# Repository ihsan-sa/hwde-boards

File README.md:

# hwde-boards

KiCad board designs made with [hwde](https://github.com/ihsan-sa/hwde), an AI PCB design skill for
Claude Code that takes a board from a written brief to a JLCPCB order. Each folder is one board's
whole workspace: the brief, research notes, architecture, parts choices, the KiCad project,
routing work, review reports, logs, and the fab package.

Every board has a part number of the form **PCB-NNNN-R**: four digits for the product, then a
revision letter. `register.yaml` lists them.

## The boards

Layers and size come from each board's KiCad file. Stage is the hwde phase recorded in the board's
`state.json`: P3 parts, P4 schematic, P7 routing, P8 verification, P9 DFM and fab outputs, P10 ordering.

| Number | What it is | Layers | Size (mm) | Stage |
|---|---|---|---|---|
| [PCB-0001-A](PCB-0001-A_stm32-blinky) | STM32F103 2-layer blinky dev board | 2 | 50 x 40 | P10 |
| [PCB-0002-A](PCB-0002-A_usb-buck) | STM32F103 4-layer USB device board with 3.3 V buck | 4 | 50 x 40 | P10 |
| [PCB-0003-A](PCB-0003-A_pd-trigger) | USB-C PD trigger, 5 A / 100 W bench board | 2 | 48 x 30 | P10 |
| [PCB-0004-A](PCB-0004-A_lumina-carrier) | LUMINA PoE ESP32 carrier | 4 | 100 x 80 | P10 |
| [PCB-0005-A](PCB-0005-A_lumina-par) | LUMINA RGB+W par light daughter board | 4 | 100 x 80 | P8, no fab package |
| [PCB-0006-A](PCB-0006-A_lumina-strobe) | LUMINA strobe daughter board | - | - | P4, no board yet |
| [PCB-0007-A](PCB-0007-A_rf-de-20m) | 20 MHz Class E GaN RF power stage, 200 W | 4 | 120 x 80 | P9, see its `fab/README.md` |
| [PCB-0008-A](PCB-0008-A_buck-5v3a) | 12 V to 5 V / 3 A synchronous buck, first attempt | - | - | closed at P3, never built |
| [PCB-0008-B](PCB-0008-B_sbuck-5v3a) | 12 V to 5 V / 3 A synchronous buck | 4 | 50 x 40 | P10 |
| [PCB-0009-A](PCB-0009-A_rf-term-150w) | 50 ohm / 150 W RF termination | 2 | 26 x 20 | P9 |
| [PCB-0010-A](PCB-0010-A_bb-buck) | Bare-bones 24 V to 5 V / 2 A buck | 2 | 35 x 25 | P9 |
| [PCB-0011-A](PCB-0011-A_bb-mcu) | Block-basics microcontroller board | 2 | 34.8 x 22.3 | P9 |
| [PCB-0012-A](PCB-0012-A_bb-ldo) | Block-basics 5 V to 3.3 V / 500 mA LDO | 2 | 34.7 x 34.7 | P9 |
| [PCB-0013-A](PCB-0013-A_bb-amp) | Block-basics bridge-sensor amplifier | 2 | 48.0 x 28.3 | P9 |
| [PCB-0014-A](PCB-0014-A_bb-adc) | Block-basics 12-bit single-channel ADC | 2 | 54.8 x 34.9 | P9 |
| [PCB-0015-A](PCB-0015-A_g0-sense) | USB-C STM32G0 temperature/humidity sensor node | 2 | 35.8 x 28.3 | P10 |
| [PCB-0016-A](PCB-0016-A_pd-trigger-lite) | Low-cost USB-C PD trigger (CH224K) | 2 | 25 x 15 | P8 |
| [PCB-0016-B](PCB-0016-B_pd-trigger-lite-dip) | The same, voltage picked with a DIP switch | 2 | 25 x 21 | P9 |
| [PCB-0017-A](PCB-0017-A_stereo-class-d-amp) | TPA3118D2 stereo class-D amplifier, 12 V | 2 | 53.5 x 36.8 | P7 |
| [PCB-0018-A](PCB-0018-A_bldc-motor-driver) | 3-phase BLDC motor driver, 10-28 V, 10 A RMS/phase, STM32G4 FOC | 4 | 78 x 78 | P9 |
| [PCB-0020-A](PCB-0020-A_esp32c3-node) | ESP32-C3 WiFi/BLE sensor node, USB-C, 1S LiPo, BME280 | 2 | 26 x 38 | P8 |
| [PCB-0021-A](PCB-0021-A_lipo-boost) | Single-cell LiPo charger + 5 V / 1 A boost with load sharing | 2 | 53.9 x 38.8 | P9 |

All boards with a fab package are 1.6 mm thick.

## Where things are in a board folder

- `kicad/` the KiCad project (`.kicad_pro`, `.kicad_sch`, `.kicad_pcb`); it was made with KiCad 10, so open it with KiCad 10.
- `fab/` the order package: `<folder>_gerbers.zip`, `BOM.csv` and `CPL.csv` in JLCPCB's format.
- `reports/` review reports, renders, a schematic PDF for every board that has a schematic, and a
  design document PDF for most of them.
- `brief/`, `requirements.md`, `research/`, `architecture/`, `parts/` why the board is the way it is.
- `state.json` the phase, the gates that passed, and every decision hwde recorded.

## Ordering a board from JLCPCB

1. On jlcpcb.com, start a PCB order and upload the board's `fab/<folder>_gerbers.zip`. Set the
   layer count and thickness to match the table above.
2. To have JLCPCB assemble it, turn on PCB Assembly and upload `fab/BOM.csv` as the BOM and
   `fab/CPL.csv` as the pick-and-place file.
3. Check the part matches and the placement preview before you pay. Stock changes, so a part may
   need a substitute from the same footprint.

Read the board's reports first. Unless a board's own documents say it was built and tested, treat
the design as unverified on real hardware.

## What is not included

- **3D models.** Vendor STEP and WRL models are not redistributed, so footprints that pointed at
  them show no 3D body in KiCad's 3D viewer. The copper, silkscreen and fab outputs are unaffected.
- **Datasheets and app notes.** Vendor PDFs and copies of vendor pages are left out. The research
  notes and `parts/` records still cite them by name and part number.
- Order and shipment records, and a few design documents whose text carried private details.
  Their LaTeX sources are still under `reports/`.

Some files keep absolute paths from the machine a board was designed on (for example
`C:/Users/<user>/...`). They are records of a run and are not needed to open the design.

## License

MIT, see [LICENSE](LICENSE).

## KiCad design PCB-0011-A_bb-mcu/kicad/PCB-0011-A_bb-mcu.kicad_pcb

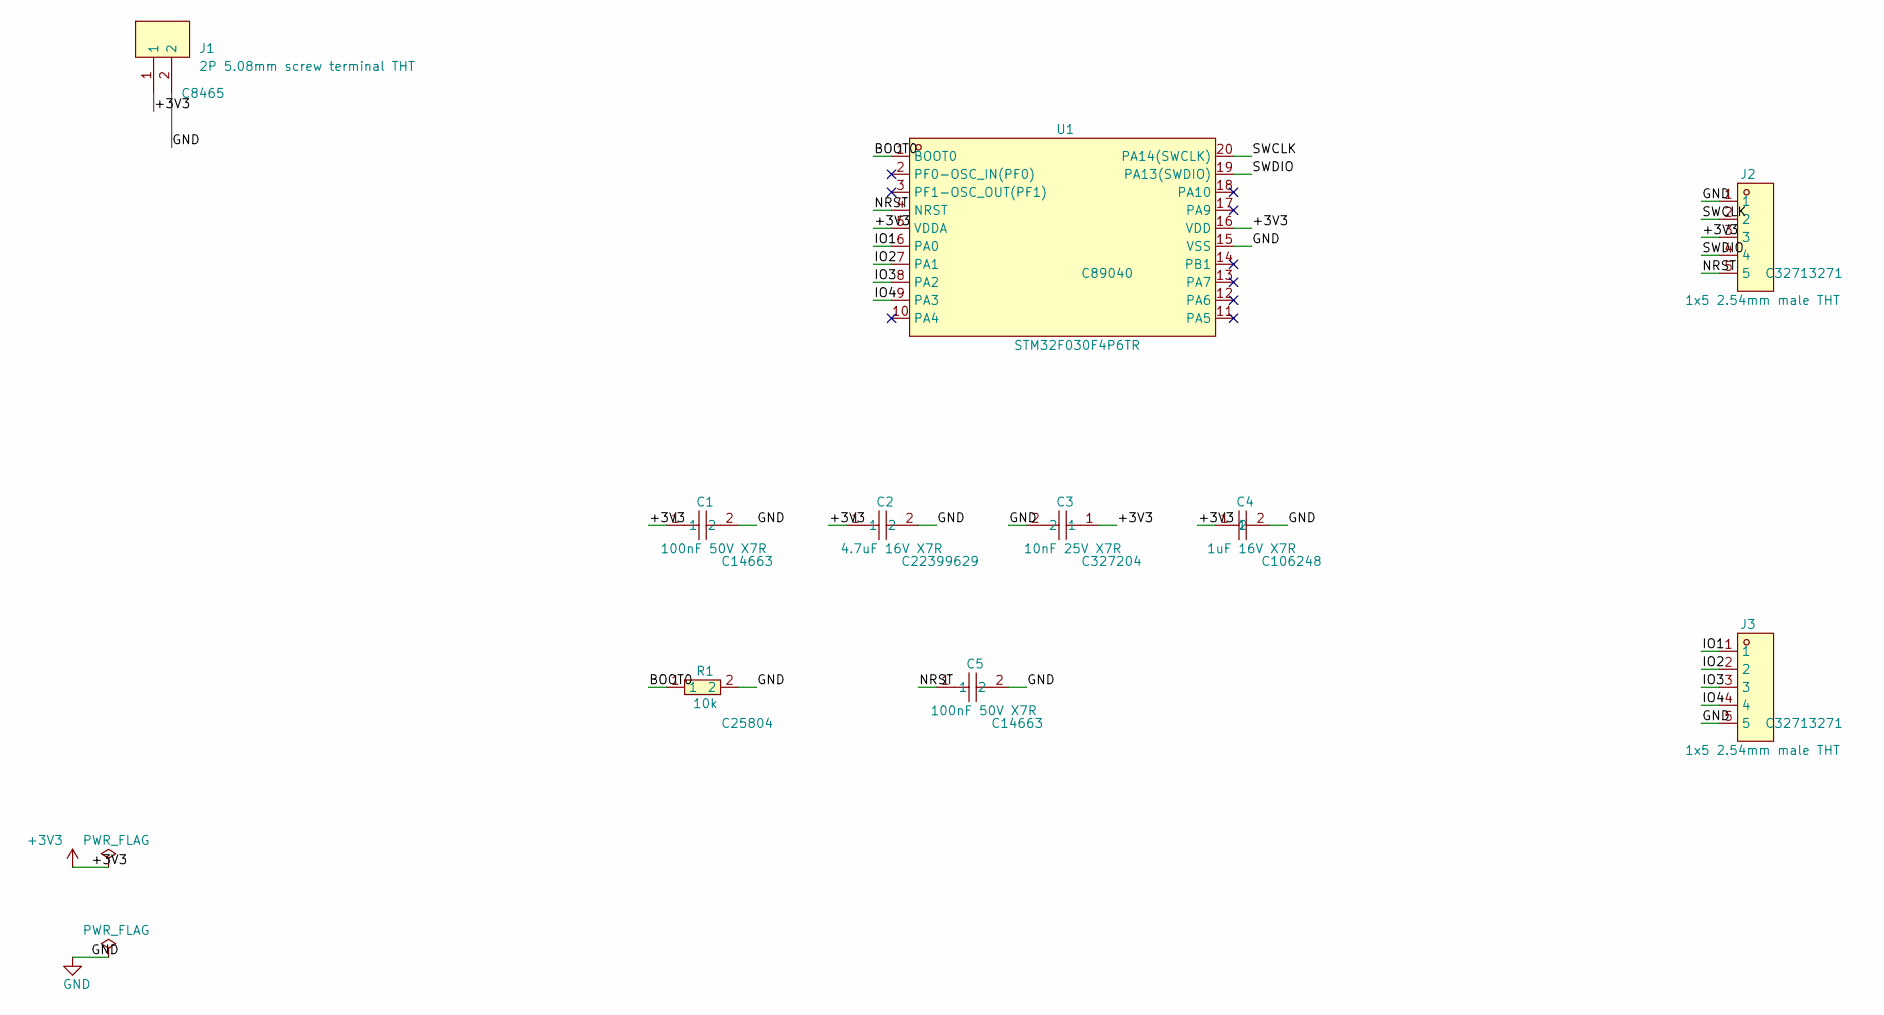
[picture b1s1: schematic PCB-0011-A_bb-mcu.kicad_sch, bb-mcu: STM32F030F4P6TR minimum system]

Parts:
C1, C5: 100nF 50V X7R; C0603; LCSC C14663
C2: 4.7uF 16V X7R; C0603; LCSC C22399629
C3: 10nF 25V X7R; C0603; LCSC C327204
C4: 1uF 16V X7R; C0603; LCSC C106248
J1: 2P 5.08mm screw terminal THT; CONN-TH_2P-P5.00_WJ500V-5.08-2P; LCSC C8465
J2, J3: 1x5 2.54mm male THT; HDR-TH_5P-P2.54-V-M; LCSC C32713271
R1: 10k; R0603; LCSC C25804
U1: STM32F030F4P6TR; SOP-20_L6.5-W4.4-P0.65-LS6.4-BL; LCSC C89040

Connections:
+3V3: C1.1, C2.1, C3.1, C4.1, J1.1, J2.3, U1.5 (VDDA), U1.16 (VDD)
/BOOT0: R1.1, U1.1 (BOOT0)
/IO1: J3.1, U1.6 (PA0)
/IO2: J3.2, U1.7 (PA1)
/IO3: J3.3, U1.8 (PA2)
/IO4: J3.4, U1.9 (PA3)
/NRST: C5.1, J2.5, U1.4 (NRST)
/SWCLK: J2.2, U1.20 (PA14(SWCLK))
/SWDIO: J2.4, U1.19 (PA13(SWDIO))
GND: C1.2, C2.2, C3.2, C4.2, C5.2, J1.2, J2.1, J3.5, R1.2, U1.15 (VSS)

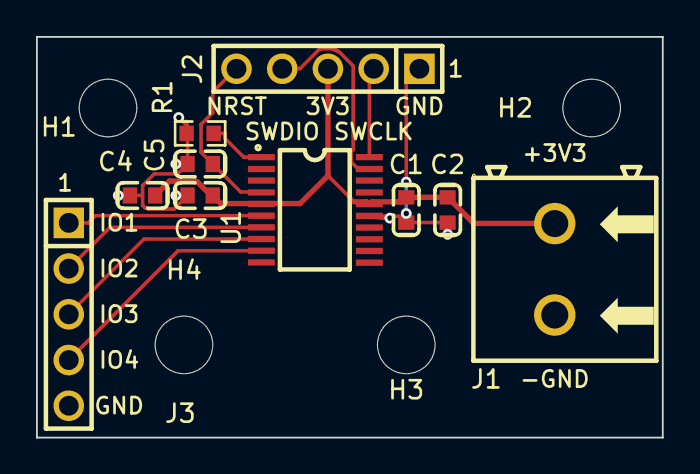
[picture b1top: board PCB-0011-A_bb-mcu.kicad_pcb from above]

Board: 2 copper layers, 34.8 x 22.3 mm, 14 parts (0 on the bottom side), 10 nets.

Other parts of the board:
H1, H2, H3, H4: MountingHole_3.2mm_M3

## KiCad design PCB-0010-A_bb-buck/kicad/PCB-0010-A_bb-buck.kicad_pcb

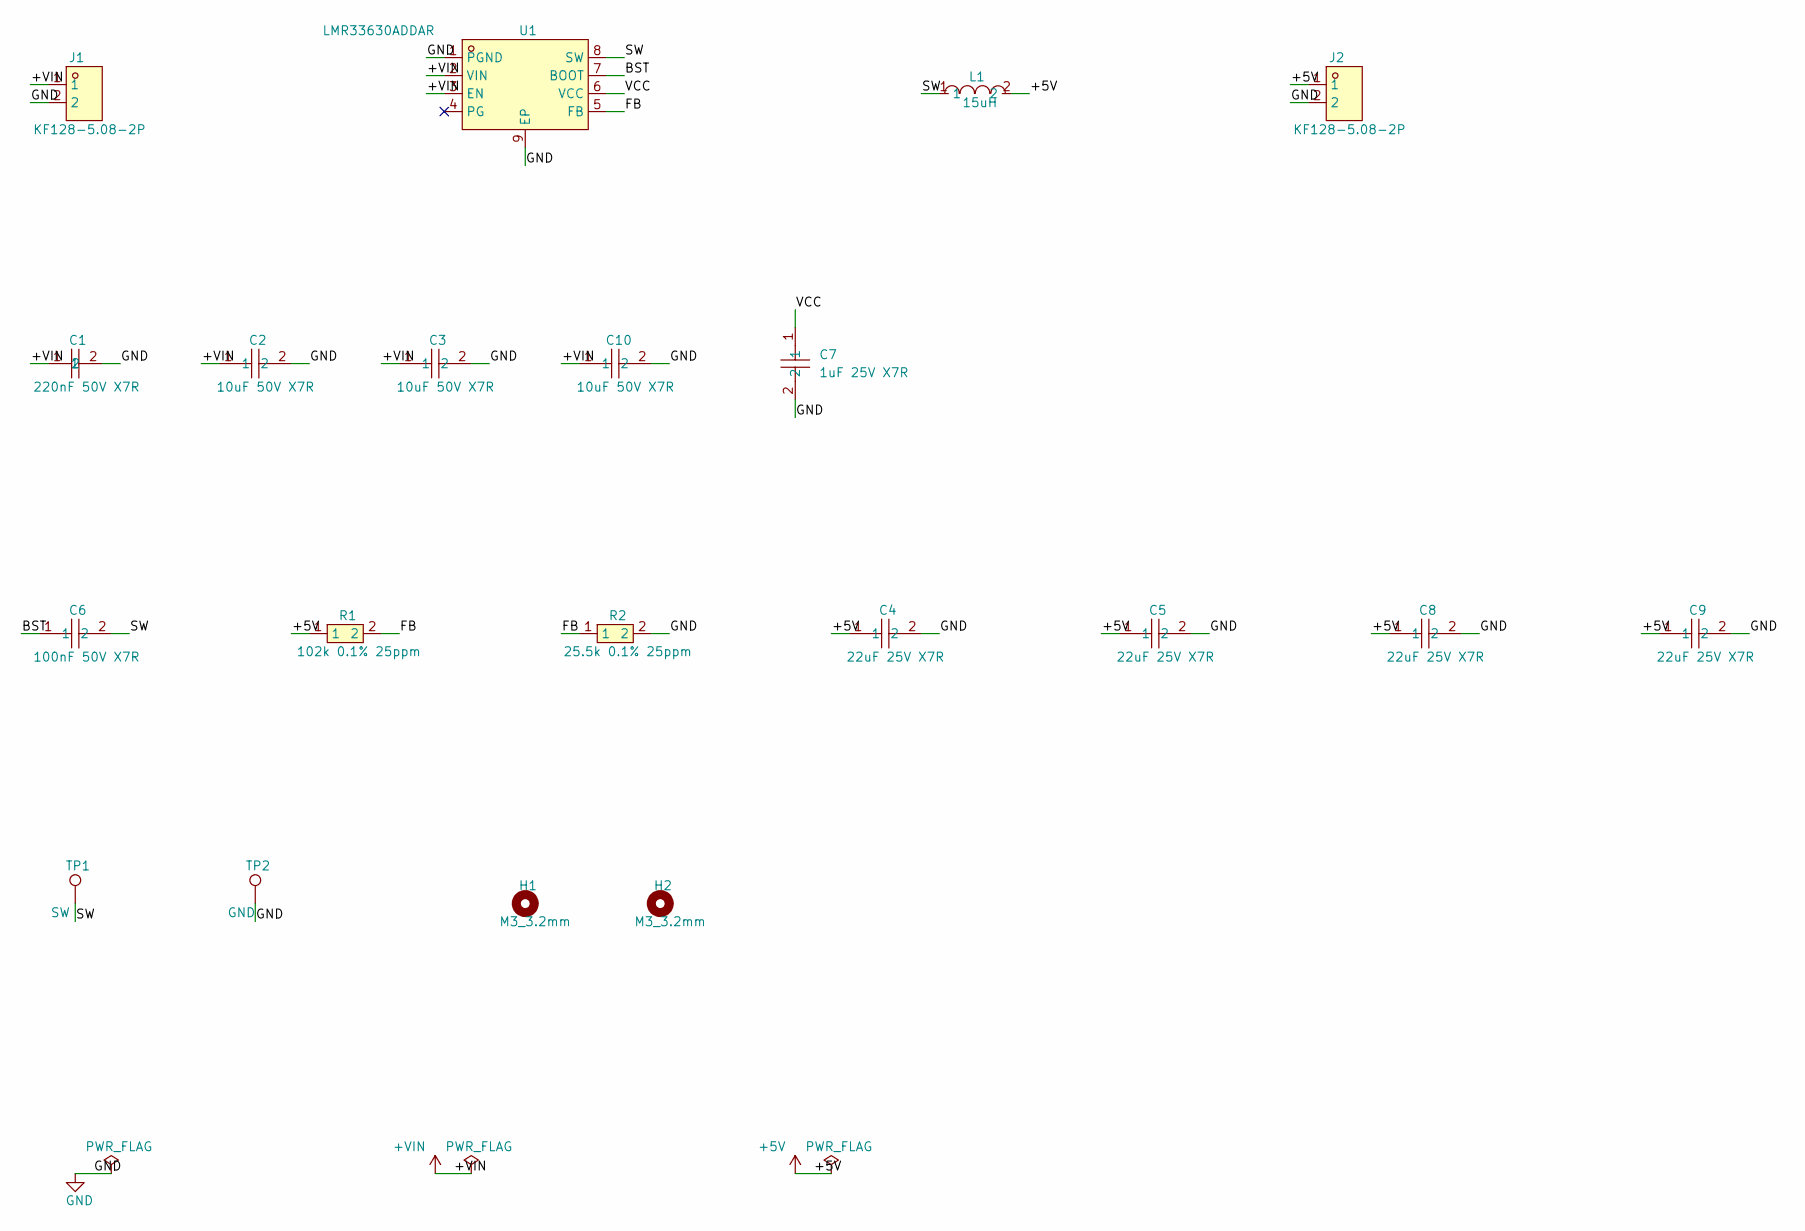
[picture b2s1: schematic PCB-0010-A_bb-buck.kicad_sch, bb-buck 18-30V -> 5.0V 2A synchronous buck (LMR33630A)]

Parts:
C1: 220nF 50V X7R; C0603; LCSC C107083
C2, C3, C10: 10uF 50V X7R; C1210; LCSC C2918502
C4, C5, C8, C9: 22uF 25V X7R; C1210; LCSC C2918511
C6: 100nF 50V X7R; C0603; LCSC C14663
C7: 1uF 25V X7R; C0603; LCSC C106858
H1, H2: M3_3.2mm; MountingHole_3.2mm_M3
J1, J2: KF128-5.08-2P; CONN-TH_P5.08_KF128-5.08-2P; LCSC C474952
L1: 15uH; IND-SMD_L12.5-W12.5_RLF12545T; LCSC C40000
R1: 102k 0.1% 25ppm; R0603; LCSC C861068
R2: 25.5k 0.1% 25ppm; R0603; LCSC C861257
TP1: SW; TestPoint_Pad_D1.5mm
TP2: GND; TestPoint_Pad_D1.5mm
U1: LMR33630ADDAR; ESOP-8_L4.9-W3.9-P1.27-LS6.0-TL-EP; LCSC C841384

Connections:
+5V: C4.1, C5.1, C8.1, C9.1, J2.1, L1.2, R1.1
+VIN: C1.1, C2.1, C3.1, C10.1, J1.1, U1.2 (VIN), U1.3 (EN)
/BST: C6.1, U1.7 (BOOT)
/FB: R1.2, R2.1, U1.5 (FB)
/SW: C6.2, L1.1, TP1.1, U1.8 (SW)
/VCC: C7.1, U1.6 (VCC)
GND: C1.2, C2.2, C3.2, C4.2, C5.2, C7.2, C8.2, C9.2, C10.2, J1.2, J2.2, R2.2, TP2.1, U1.1 (PGND), U1.9 (EP)

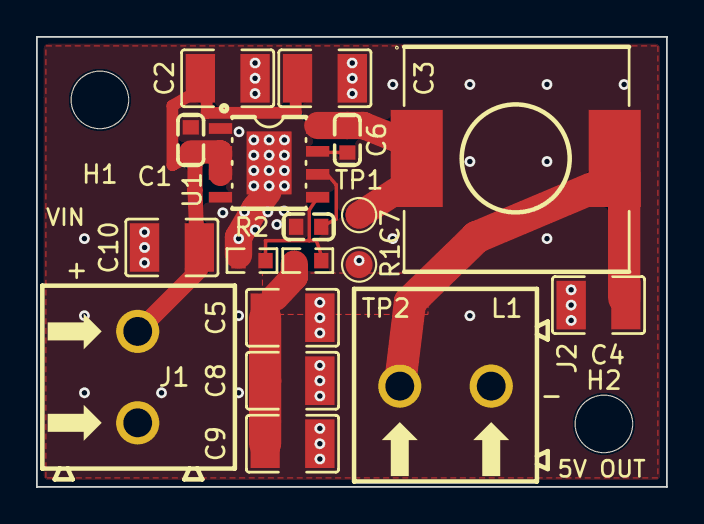
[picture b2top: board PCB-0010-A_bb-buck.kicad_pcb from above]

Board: 2 copper layers, 35.0 x 25.0 mm, 20 parts (0 on the bottom side), 7 nets.

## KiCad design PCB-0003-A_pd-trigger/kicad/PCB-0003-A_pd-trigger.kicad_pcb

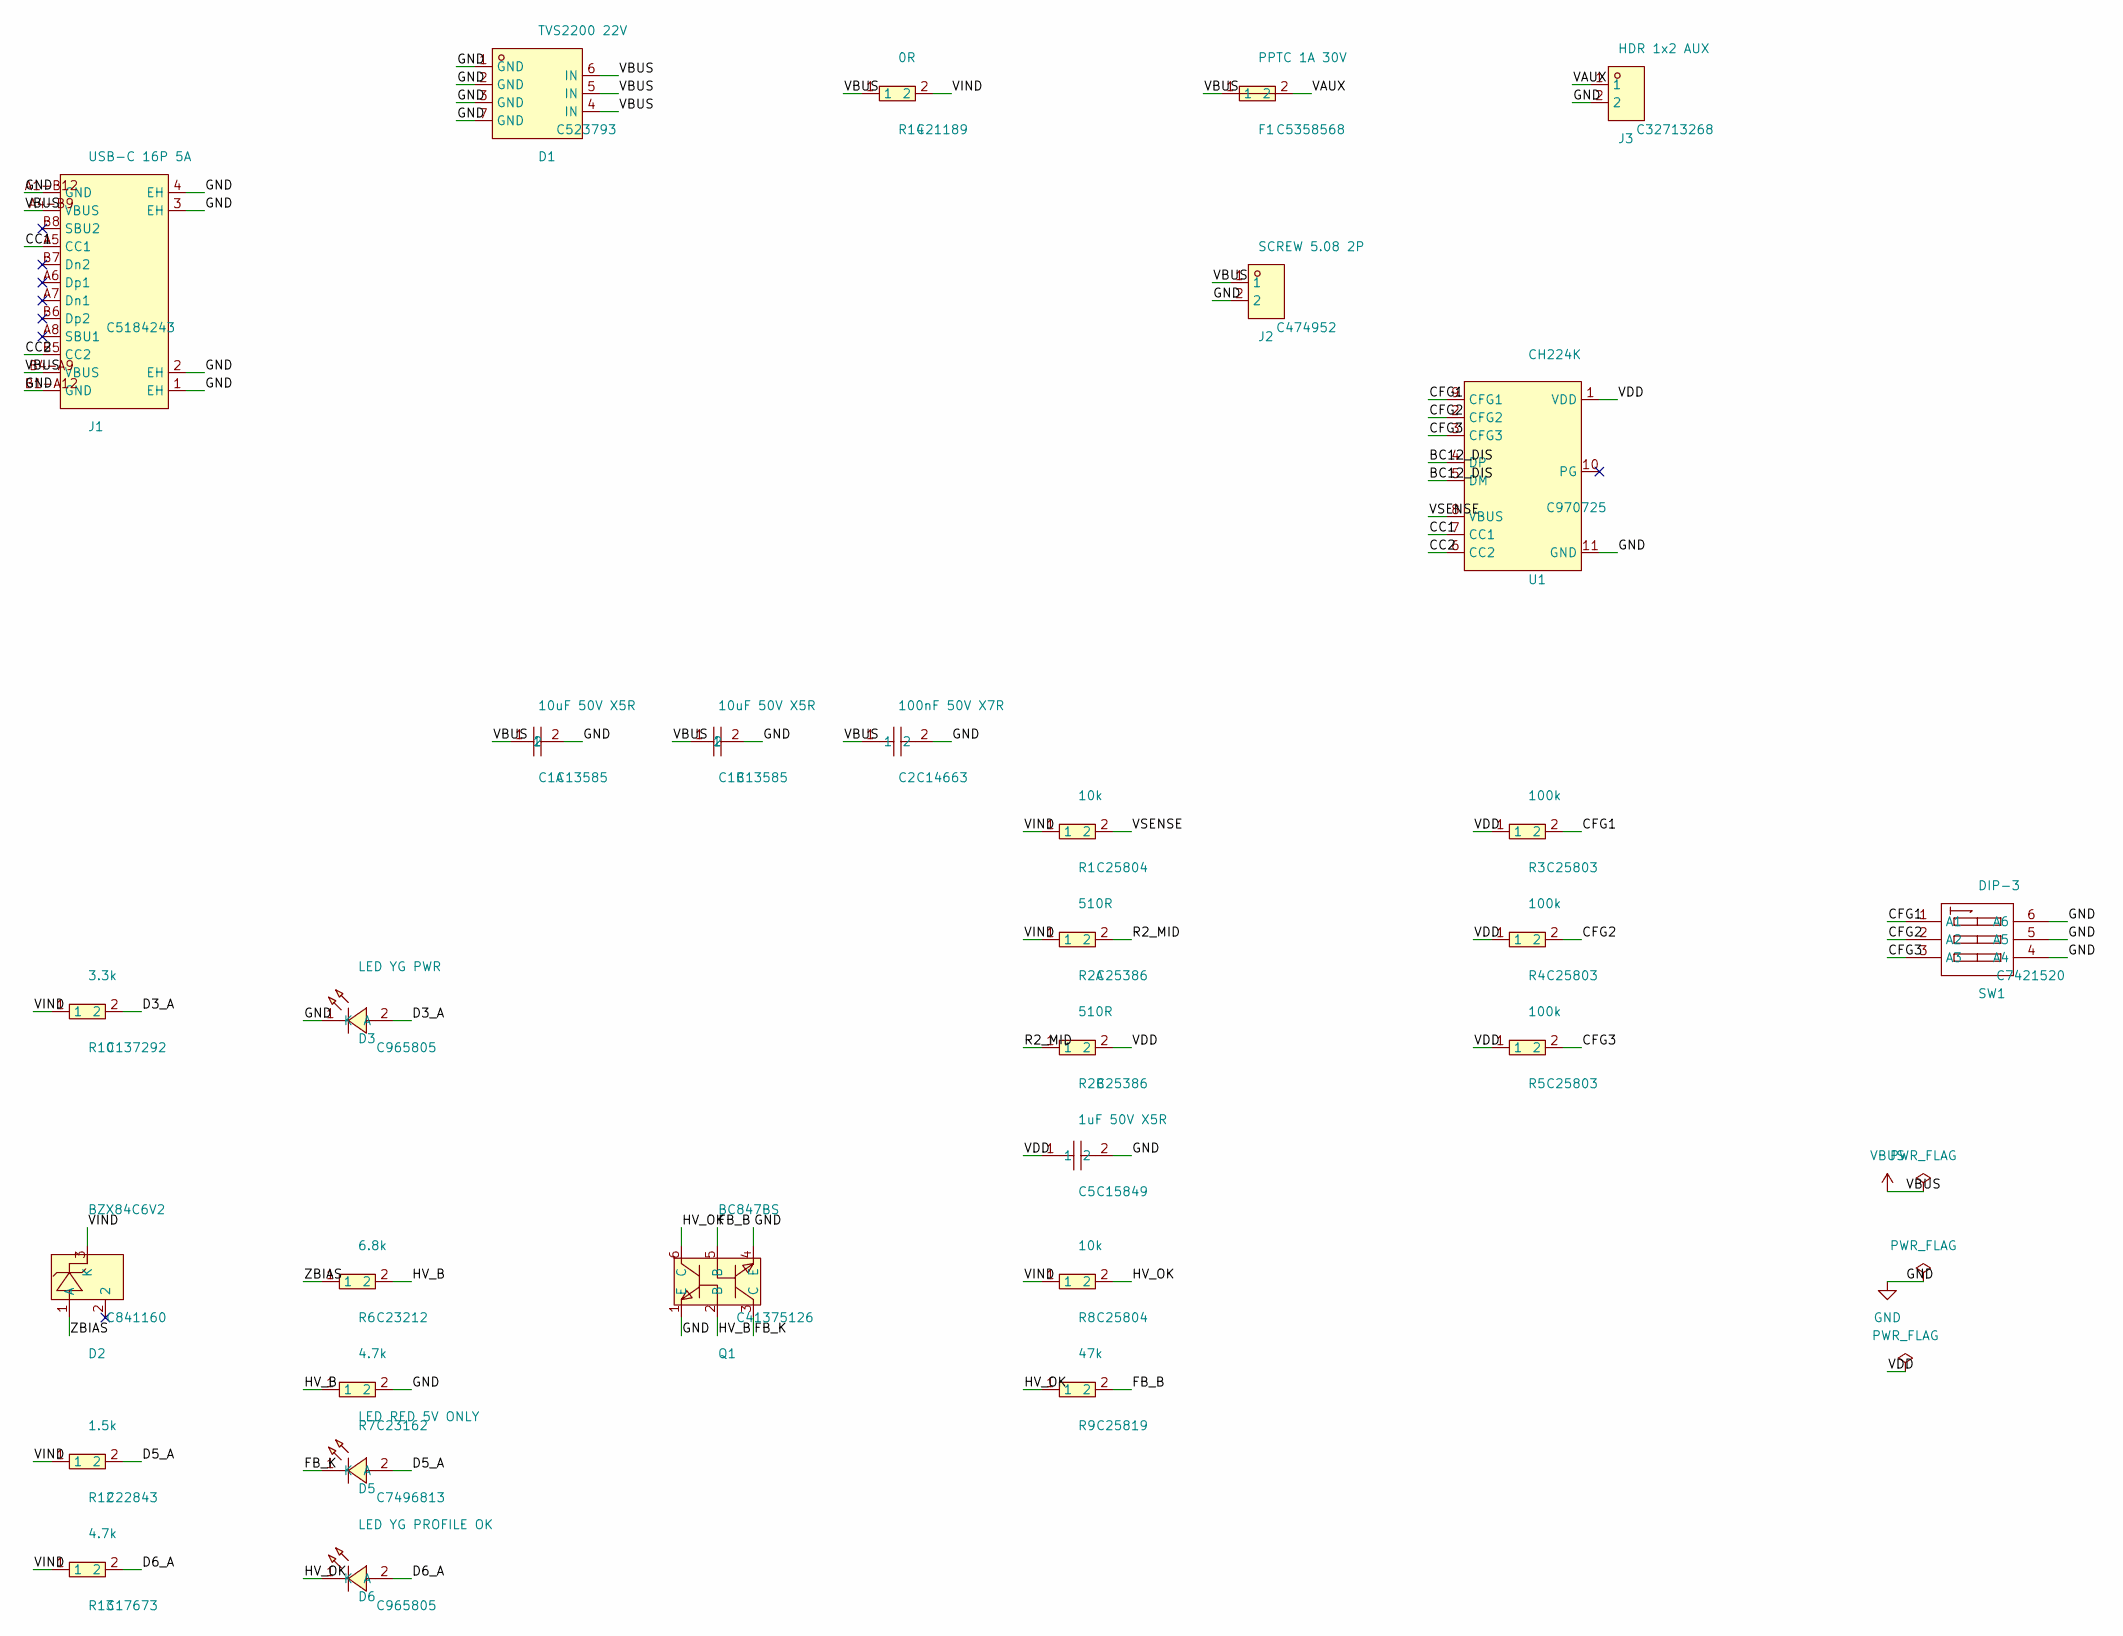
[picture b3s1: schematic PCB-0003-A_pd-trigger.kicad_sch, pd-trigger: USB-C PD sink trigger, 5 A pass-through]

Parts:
C1A, C1B: 10uF 50V X5R; C1206; LCSC C13585
C2: 100nF 50V X7R; C0603; LCSC C14663
C5: 1uF 50V X5R; C0603; LCSC C15849
D1: TVS2200 22V; WSON-6_L2.0-W2.0-P0.65-BL-EP; LCSC C523793
D2: BZX84C6V2; SOT-23-3_L2.9-W1.3-P1.90-LS2.4-BR; LCSC C841160
D3: LED YG PWR; LED0603-RD_GREEN; LCSC C965805
D5: LED RED 5V ONLY; LED0603-RD; LCSC C7496813
D6: LED YG PROFILE OK; LED0603-RD_GREEN; LCSC C965805
F1: PPTC 1A 30V; F1206; LCSC C5358568
J1: USB-C 16P 5A; USB-C-SMD_MC-311D; LCSC C5184243
J2: SCREW 5.08 2P; CONN-TH_P5.08_KF128-5.08-2P; LCSC C474952
J3: HDR 1x2 AUX; HDR-TH_2P-P2.54-V-M-3; LCSC C32713268
Q1: BC847BS; SOT-363-6_L2.2-W1.3-P0.65-LS2.1-BL; LCSC C41375126
R1, R8: 10k; R0603; LCSC C25804
R2A, R2B: 510R; R1206; LCSC C25386
R3, R4, R5: 100k; R0603; LCSC C25803
R6: 6.8k; R0603; LCSC C23212
R7: 4.7k; R0603; LCSC C23162
R9: 47k; R0603; LCSC C25819
R10: 3.3k; R1206; LCSC C137292
R12: 1.5k; R0603; LCSC C22843
R13: 4.7k; R0805; LCSC C17673
R14: 0R; R0603; LCSC C21189
SW1: DIP-3; SW-SMD_6P-L7.6-W6.0-P2.54-LS9.3-BL; LCSC C7421520
U1: CH224K; ESSOP-10_L4.9-W3.9-P1.0-LS6.0-TL-EP; LCSC C970725

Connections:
/BC12_DIS: U1.4 (DP), U1.5 (DM)
/CC1: J1.A5 (CC1), U1.7 (CC1)
/CC2: J1.B5 (CC2), U1.6 (CC2)
/CFG1: R3.2, SW1.1 (A1), U1.9 (CFG1)
/CFG2: R4.2, SW1.2 (A2), U1.2 (CFG2)
/CFG3: R5.2, SW1.3 (A3), U1.3 (CFG3)
/D3_A: D3.2 (A), R10.2
/D5_A: D5.2 (A), R12.2
/D6_A: D6.2 (A), R13.2
/FB_B: Q1.5 (B), R9.2
/FB_K: D5.1 (K), Q1.3 (C)
/HV_B: Q1.2 (B), R6.2, R7.1
/HV_OK: D6.1 (K), Q1.6 (C), R8.2, R9.1
/R2_MID: R2A.2, R2B.1
/VAUX: F1.2, J3.1
/VDD: C5.1, R2B.2, R3.1, R4.1, R5.1, U1.1 (VDD)
/VIND: D2.3 (K), R1.1, R2A.1, R8.1, R10.1, R12.1, R13.1, R14.2
/VSENSE: R1.2, U1.8 (VBUS)
/ZBIAS: D2.1 (A), R6.1
GND: C1A.2, C1B.2, C2.2, C5.2, D1.1 (GND), D1.2 (GND), D1.3 (GND), D1.7 (GND), D3.1 (K), J1.1 (EH), J1.2 (EH), J1.3 (EH), J1.4 (EH), J1.A1-B12 (GND), J1.B1-A12 (GND), J2.2, J3.2, Q1.1 (E), Q1.4 (E), R7.2, SW1.4 (A4), SW1.5 (A5), SW1.6 (A6), U1.11 (GND)
VBUS: C1A.1, C1B.1, C2.1, D1.4 (IN), D1.5 (IN), D1.6 (IN), F1.1, J1.A4-B9 (VBUS), J1.B4-A9 (VBUS), J2.1, R14.1

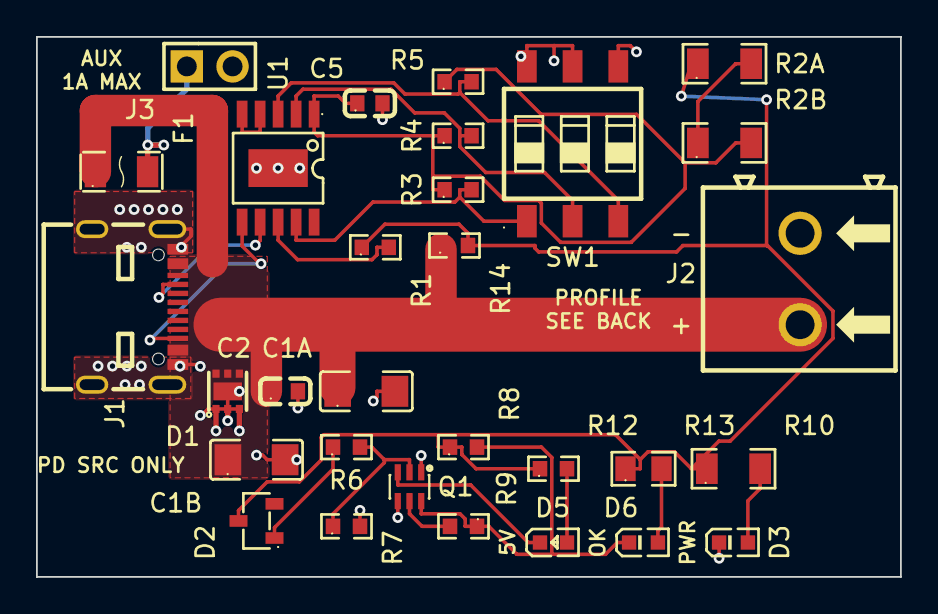
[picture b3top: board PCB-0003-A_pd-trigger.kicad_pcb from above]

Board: 2 copper layers, 48.0 x 30.0 mm, 30 parts (0 on the bottom side), 21 nets.

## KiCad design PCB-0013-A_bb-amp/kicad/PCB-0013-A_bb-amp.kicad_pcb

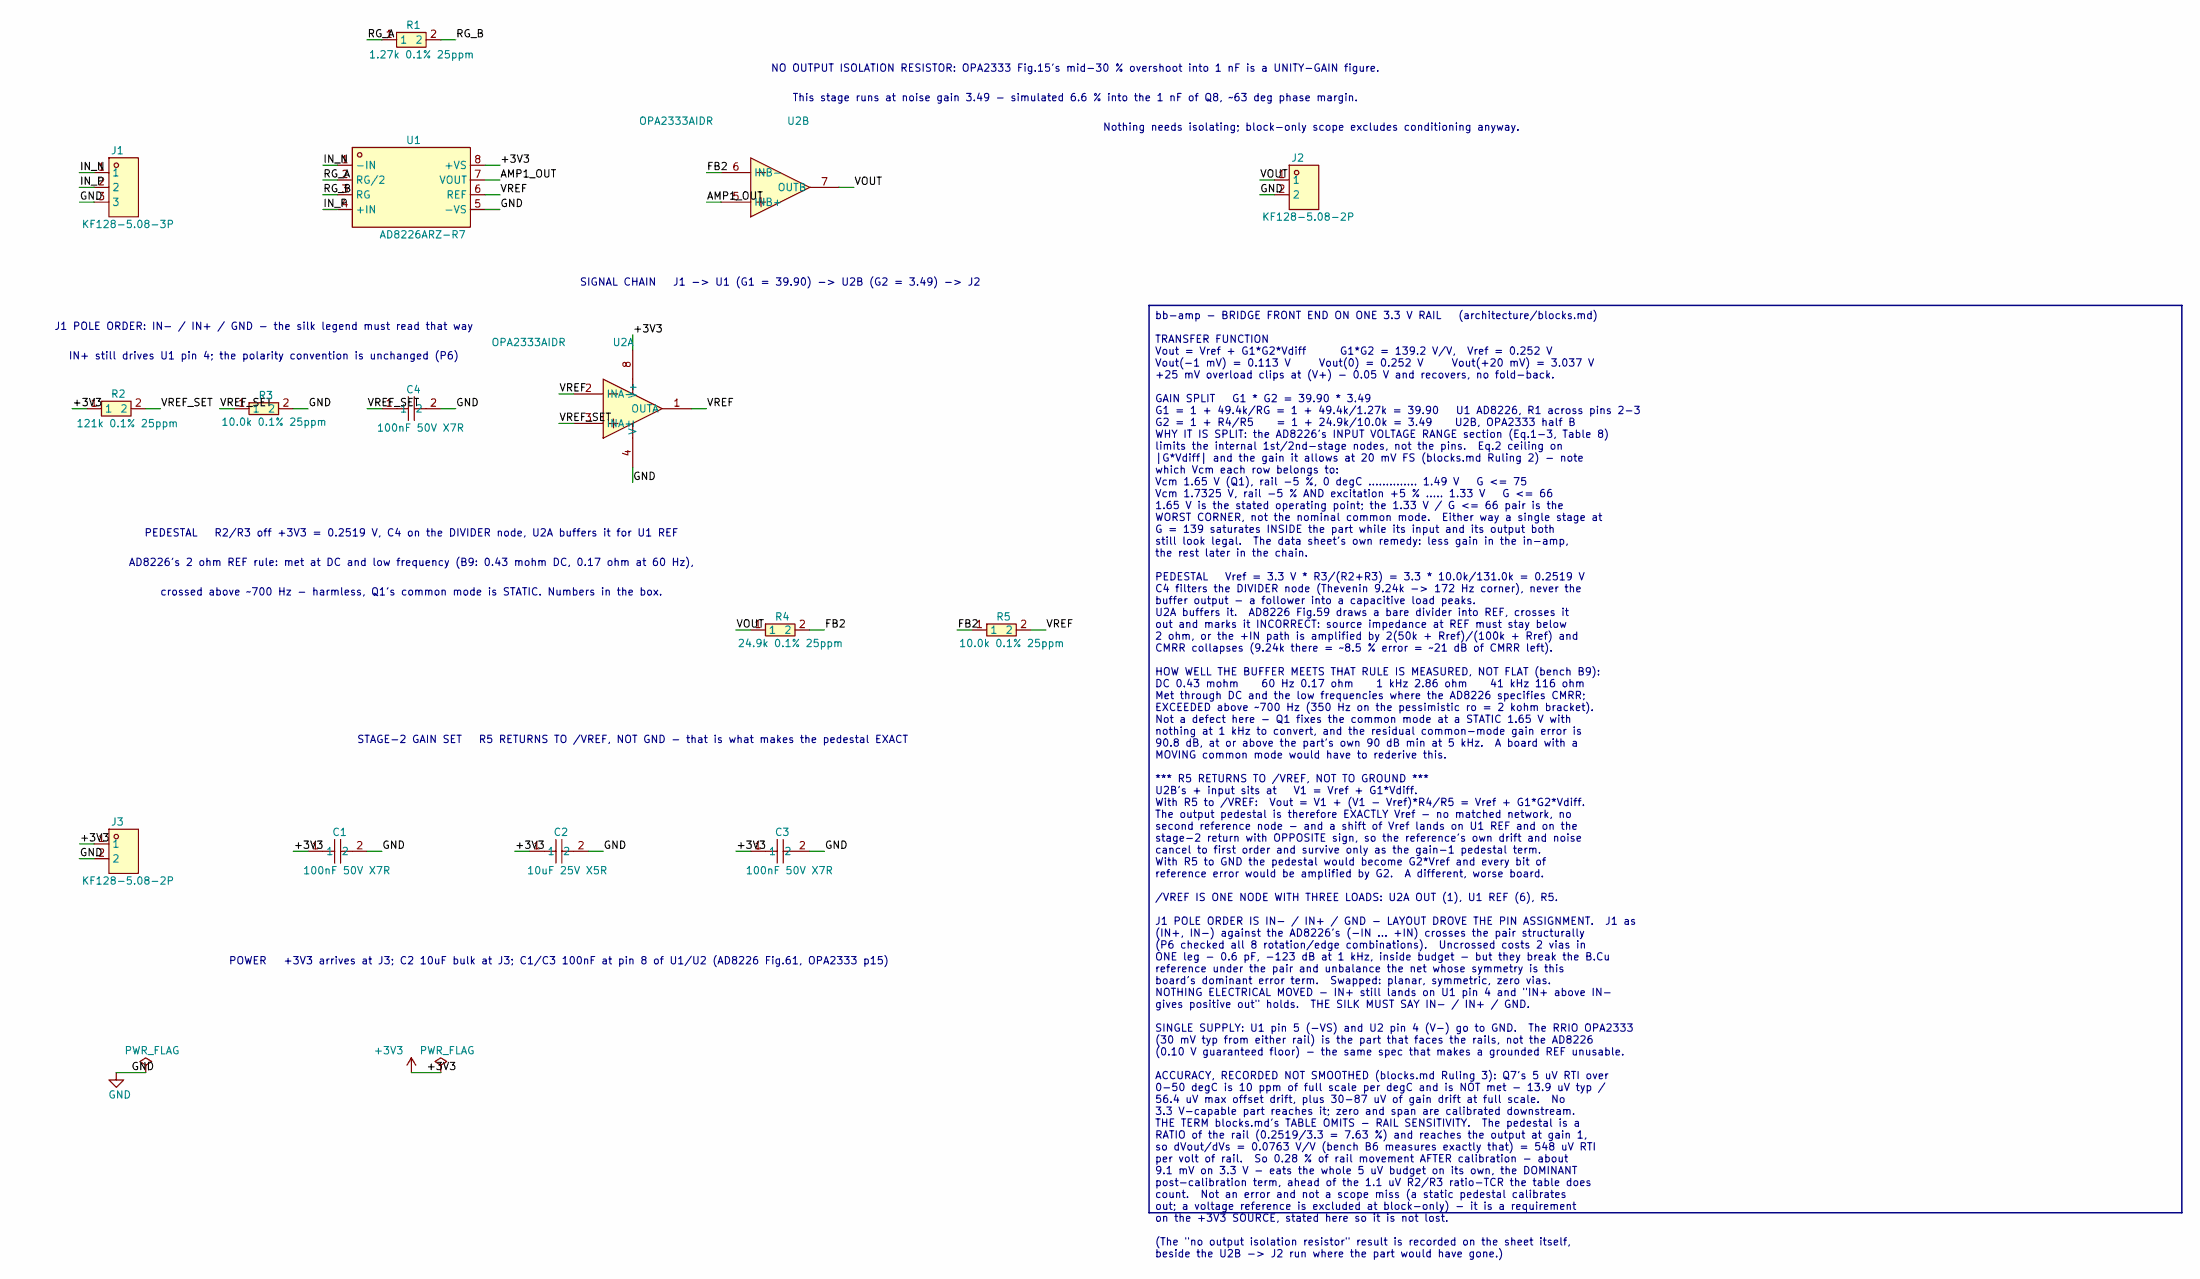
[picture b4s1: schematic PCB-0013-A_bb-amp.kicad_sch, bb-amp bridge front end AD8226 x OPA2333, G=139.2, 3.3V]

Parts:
C1, C3, C4: 100nF 50V X7R; C0603; LCSC C14663
C2: 10uF 25V X5R; C0805; LCSC C15850
J1: KF128-5.08-3P; CONN-TH_3P-P5.08_KF128-5.08-3P; LCSC C474953
J2, J3: KF128-5.08-2P; CONN-TH_P5.08_KF128-5.08-2P; LCSC C474952
R1: 1.27k 0.1% 25ppm; R0603; LCSC C861195
R2: 121k 0.1% 25ppm; R0603; LCSC C861095
R3, R5: 10.0k 0.1% 25ppm; R0603; LCSC C95204
R4: 24.9k 0.1% 25ppm; R0603; LCSC C136967
U1: AD8226ARZ-R7; SOIC-8_L5.0-W4.0-P1.27-LS6.0-BL; LCSC C34250
U2: OPA2333AIDR; SOP-8_L4.9-W3.9-P1.27-LS6.0-BL; LCSC C38732

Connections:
+3V3: C1.1, C2.1, C3.1, J3.1, R2.1, U1.8 (+VS), U2.8 (V+)
/AMP1_OUT: U1.7 (VOUT), U2.5 (INB+)
/FB2: R4.2, R5.1, U2.6 (INB-)
/IN_N: J1.1, U1.1 (-IN)
/IN_P: J1.2, U1.4 (+IN)
/RG_A: R1.1, U1.2 (RG/2)
/RG_B: R1.2, U1.3 (RG)
/VOUT: J2.1, R4.1, U2.7 (OUTB)
/VREF: R5.2, U1.6 (REF), U2.1 (OUTA), U2.2 (INA-)
/VREF_SET: C4.1, R2.2, R3.1, U2.3 (INA+)
GND: C1.2, C2.2, C3.2, C4.2, J1.3, J2.2, J3.2, R3.2, U1.5 (-VS), U2.4 (V-)

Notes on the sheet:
SIGNAL CHAIN J1 -> U1 (G1 = 39.90) -> U2B (G2 = 3.49) -> J2
J1 POLE ORDER: IN- / IN+ / GND - the silk legend must read that way
IN+ still drives U1 pin 4; the polarity convention is unchanged (P6)
NO OUTPUT ISOLATION RESISTOR: OPA2333 Fig.15's mid-30 % overshoot into 1 nF is a UNITY-GAIN figure.
This stage runs at noise gain 3.49 - simulated 6.6 % into the 1 nF of Q8, ~63 deg phase margin.
Nothing needs isolating; block-only scope excludes conditioning anyway.
PEDESTAL R2/R3 off +3V3 = 0.2519 V, C4 on the DIVIDER node, U2A buffers it for U1 REF
AD8226's 2 ohm REF rule: met at DC and low frequency (B9: 0.43 mohm DC, 0.17 ohm at 60 Hz),
crossed above ~700 Hz - harmless, Q1's common mode is STATIC. Numbers in the box.
STAGE-2 GAIN SET R5 RETURNS TO /VREF, NOT GND - that is what makes the pedestal EXACT
POWER +3V3 arrives at J3; C2 10uF bulk at J3; C1/C3 100nF at pin 8 of U1/U2 (AD8226 Fig.61, OPA2333 p15)
bb-amp - BRIDGE FRONT END ON ONE 3.3 V RAIL (architecture/blocks.md) TRANSFER FUNCTION Vout = Vref + G1*G2*Vdiff G1*G2 = 139.2 V/V, Vref = 0.252 V Vout(-1 mV) = 0.113 V Vout(0) = 0.252 V Vout(+20 mV) = 3.037 V +25 mV overload clips at (V+) - 0.05 V and recovers, no fold-back. GAIN SPLIT G1 * G2 = 3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

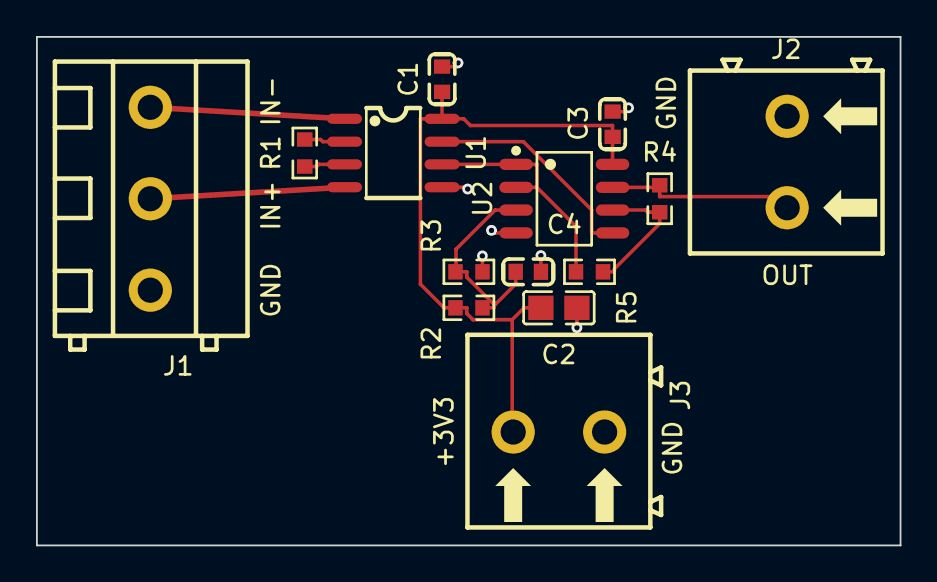
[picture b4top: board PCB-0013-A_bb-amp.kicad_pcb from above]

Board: 2 copper layers, 48.0 x 28.3 mm, 14 parts (0 on the bottom side), 11 nets.

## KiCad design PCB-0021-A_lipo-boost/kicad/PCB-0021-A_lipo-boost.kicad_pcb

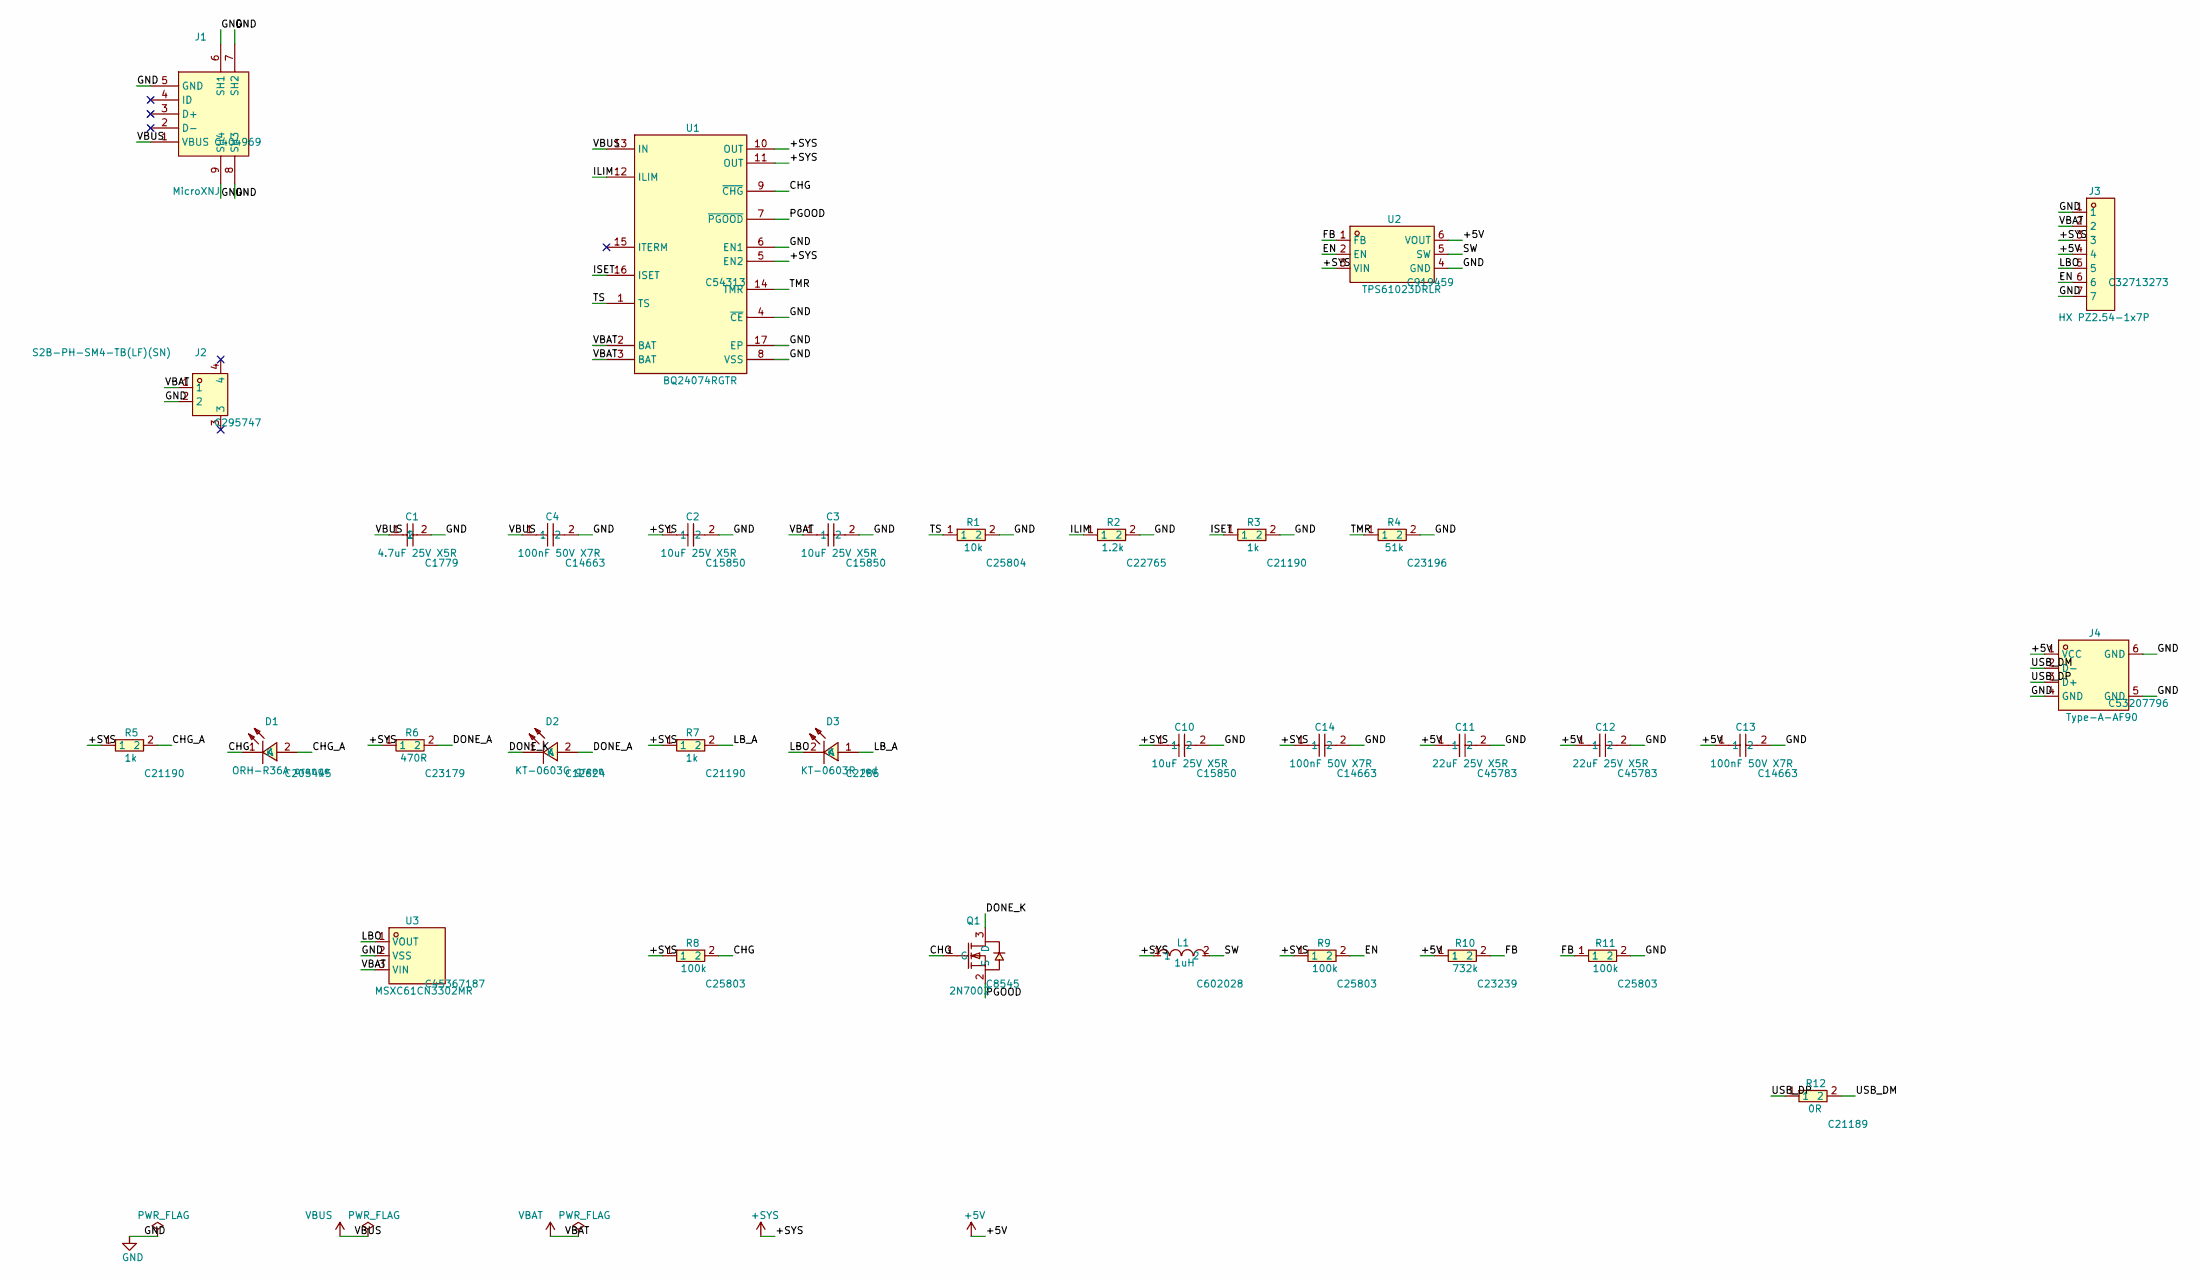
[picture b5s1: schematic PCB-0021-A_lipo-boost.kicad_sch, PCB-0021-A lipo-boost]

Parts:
C1: 4.7uF 25V X5R; C0805; LCSC Part C1779
C2, C3, C10: 10uF 25V X5R; C0805; LCSC Part C15850
C4, C13, C14: 100nF 50V X7R; C0603; LCSC Part C14663
C11, C12: 22uF 25V X5R; C0805; LCSC Part C45783
D1: ORH-R36A orange; LED0603-RD; LCSC Part C205445
D2: KT-0603G green; LED0603-RD; LCSC Part C12624
D3: KT-0603R red; LED-SMD_L1.6-W0.8-R-RD; LCSC Part C2286
J1: MicroXNJ; MICRO-USB-SMD_MICROXNJ_1; LCSC Part C404969
J2: S2B-PH-SM4-TB(LF)(SN); CONN-SMD_P2.00_S2B-PH-SM4-TB-LF-SN; LCSC Part C295747
J3: HX PZ2.54-1x7P; HDR-TH_7P-P2.54-V-M; LCSC Part C32713273
J4: Type-A-AF90; USB-A-TH_U-A-24DD-Y-13; LCSC Part C53207796
L1: 1uH; IND-SMD_L4.0-W4.0; LCSC Part C602028
Q1: 2N7002; SOT-23-3_L2.9-W1.3-P1.90-LS2.4-BR; LCSC Part C8545
R1: 10k; R0603; LCSC Part C25804
R2: 1.2k; R0603; LCSC Part C22765
R3, R5, R7: 1k; R0603; LCSC Part C21190
R4: 51k; R0603; LCSC Part C23196
R6: 470R; R0603; LCSC Part C23179
R8, R9, R11: 100k; R0603; LCSC Part C25803
R10: 732k; R0603; LCSC Part C23239
R12: 0R; R0603; LCSC Part C21189
U1: BQ24074RGTR; QFN-16_L3.0-W3.0-P0.50-TL-EP1.7; LCSC Part C54313
U2: TPS61023DRLR; SOT-563_L1.6-W1.2-P0.50-LS1.6-BR; LCSC Part C919459
U3: MSXC61CN3302MR; SOT-23-3_L2.9-W1.6-P1.90-LS2.8-BR; LCSC Part C45367187

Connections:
+5V: C11.1, C12.1, C13.1, J3.4, J4.1 (VCC), R10.1, U2.6 (VOUT)
+SYS: C2.1, C10.1, C14.1, J3.3, L1.1, R5.1, R6.1, R7.1, R8.1, R9.1, U1.5 (EN2), U1.10 (OUT), U1.11 (OUT), U2.3 (VIN)
/CHG: D1.1 (K), Q1.1 (G), R8.2, U1.9 (~CHG)
/CHG_A: D1.2 (A), R5.2
/DONE_A: D2.2 (A), R6.2
/DONE_K: D2.1 (K), Q1.3 (D)
/EN: J3.6, R9.2, U2.2 (EN)
/FB: R10.2, R11.1, U2.1 (FB)
/ILIM: R2.1, U1.12 (ILIM)
/ISET: R3.1, U1.16 (ISET)
/LBO: D3.2 (K), J3.5, U3.1 (VOUT)
/LB_A: D3.1 (A), R7.2
/PGOOD: Q1.2 (S), U1.7 (~PGOOD)
/SW: L1.2, U2.5 (SW)
/TMR: R4.1, U1.14 (TMR)
/TS: R1.1, U1.1 (TS)
/USB_DM: J4.2 (D-), R12.2
/USB_DP: J4.3 (D+), R12.1
GND: C1.2, C2.2, C3.2, C4.2, C10.2, C11.2, C12.2, C13.2, C14.2, J1.5 (GND), J1.6 (SH1), J1.7 (SH2), J1.8 (SH3), J1.9 (SH4), J2.2, J3.1, J3.7, J4.4 (GND), J4.5 (GND), J4.6 (GND), R1.2, R2.2, R3.2, R4.2, R11.2, U1.4 (~CE), U1.6 (EN1), U1.8 (VSS), U1.17 (EP), U2.4 (GND), U3.2 (VSS)
VBAT: C3.1, J2.1, J3.2, U1.2 (BAT), U1.3 (BAT), U3.3 (VIN)
VBUS: C1.1, C4.1, J1.1 (VBUS), U1.13 (IN)

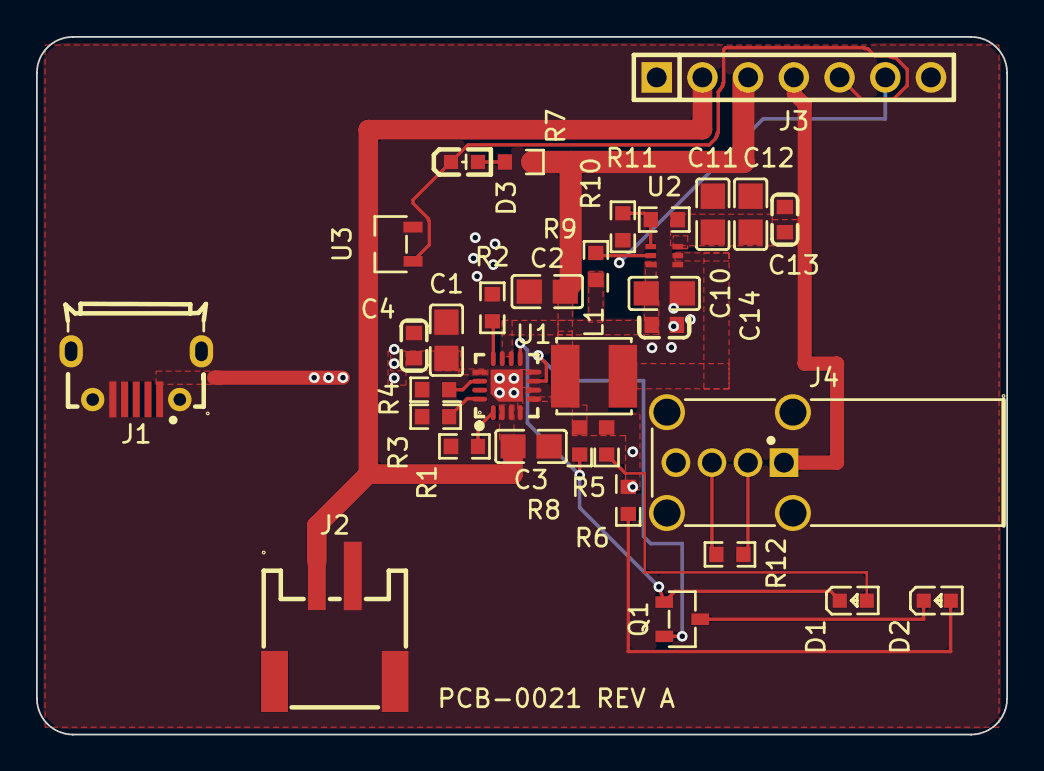
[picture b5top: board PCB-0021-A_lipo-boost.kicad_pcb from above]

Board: 2 copper layers, 53.9 x 38.8 mm, 33 parts (0 on the bottom side), 21 nets.
